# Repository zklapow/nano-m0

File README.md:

# NANO-M0

This repository contains the CAD files and sample code for the NANO-M0 dev board.

The KiCad board files can be found in the `cad` directory and source code for the sample program that ships with the NANO-M0 can be found in `src`

## License

Both the CAD and software files for the NANO-M0 are licensed under the [Apache 2.0 License](http://www.apache.org/licenses/LICENSE-2.0).

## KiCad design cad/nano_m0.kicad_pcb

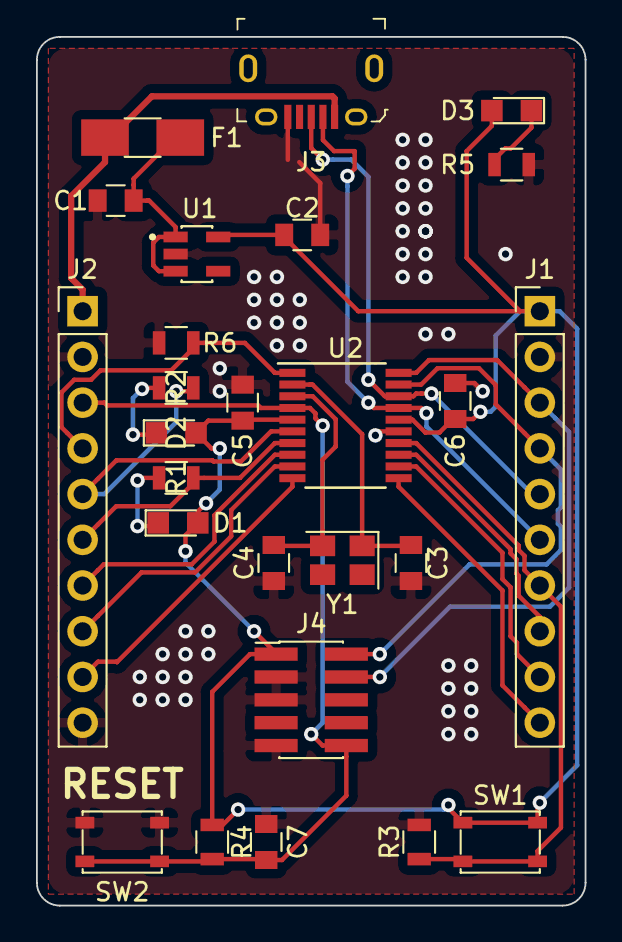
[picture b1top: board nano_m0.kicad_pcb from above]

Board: 2 copper layers, 30.5 x 48.3 mm, 26 parts (0 on the bottom side), 24 nets.

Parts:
C1, C5, C6: 1uF; C_0805
C2: 2.2uF; C_0805
C3, C4: 22pF; C_0805
C7: 0.1uF; C_0805
D1, D2: LED; LED_0805
D3: PWR; LED_0805
F1: 500mA; Fuse_SMD1206_HandSoldering
J1, J2: Conn_01x10; Pin_Header_Straight_1x10_Pitch2.54mm
J3: USB_B_Micro; USB_Micro_B_Female_10118194-0001LF
J4: SWD; Pin_Header_Straight_2x05_Pitch1.27mm_SMD
R1, R2, R5: 100; R_0805
R3, R4, R6: 10k; R_0805
SW1, SW2: SW_SPST; SW_SPST_PTS810
U1: AP2112K-3.3TRG1; SOT95P285X140-5N
U2: STM32F0706P6; TSSOP-20_4.4x6.5mm_Pitch0.65mm
Y1: Crystal; Crystal_SMD_SeikoEpson_TSX3225-4pin_3.2x2.5mm

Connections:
+3V3: C2.1, C5.1, C6.1, D1.2, D2.2, D3.2, J1.1, J4.1, R4.1, SW1.1, U1.5, U2.5, U2.16
+5V: F1.2, J2.1, J3.1
/BOOT: J2.4, R6.1, U2.1
/NRST: C7.1, J2.3, J4.10, R4.2, SW2.2, U2.4
/OSC_IN: C3.1, U2.2, Y1.1
/OSC_OUT: C4.1, U2.3, Y1.2
/PA0: J2.5, R2.2, U2.6
/PA1: J2.6, R1.2, U2.7
/PA2: J2.7, U2.8
/PA3: J2.8, U2.9
/PA4: J2.9, U2.10
/PA5: J1.10, U2.11
/PA6: J1.9, U2.12
/PA7: J1.8, U2.13
/PA13: J1.4, J4.2, U2.19
/PA14: J1.3, J4.4, U2.20
/PB1: J1.7, R3.1, SW1.2, U2.14
/USB_N: J1.6, J3.2, U2.17
/USB_P: J1.5, J3.3, U2.18
GND: C1.2, C2.2, C3.2, C4.2, C5.2, C6.2, C7.2, J1.2, J2.2, J2.10, J3.5, J4.3, J4.5, J4.9, R3.2, R5.2, R6.2, SW2.1, U1.2, U2.15
unnamed: C1.1, F1.1, U1.1, U1.3
unnamed: D1.1, R1.1
unnamed: D2.1, R2.1
unnamed: D3.1, R5.1

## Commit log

2018-12-09 first pass at pcb
2018-12-09 simple blinky program
2018-12-11 bad ws2812b driver
2018-12-19 changes to crystal
2018-12-23 messing with PWM
2018-12-25 pulse leds
2018-12-25 use newer hal
2019-02-09 board v2
2019-03-08 final v3 board
2019-03-08 remove ignored files
2019-03-08 update example
2019-03-08 update schematic symbols to kicad5
